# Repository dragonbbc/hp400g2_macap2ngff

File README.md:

# HP ProDesk 400 G2 Desktop Mini PC专用的94360CS2转接卡
将网卡接口往SSD移动了一点，完美避开电容

网卡的座子找了好久也没找到到哪里可以买到（有知道的兄弟烦请告知），现在是从别的转接卡上拆了一个装过去的
# 安装效果图

# 食用方法
直接下载gerber拿去JLC打板就好，板厚选0.8，不做沉金工艺的话5元包邮即可，土豪请随意。

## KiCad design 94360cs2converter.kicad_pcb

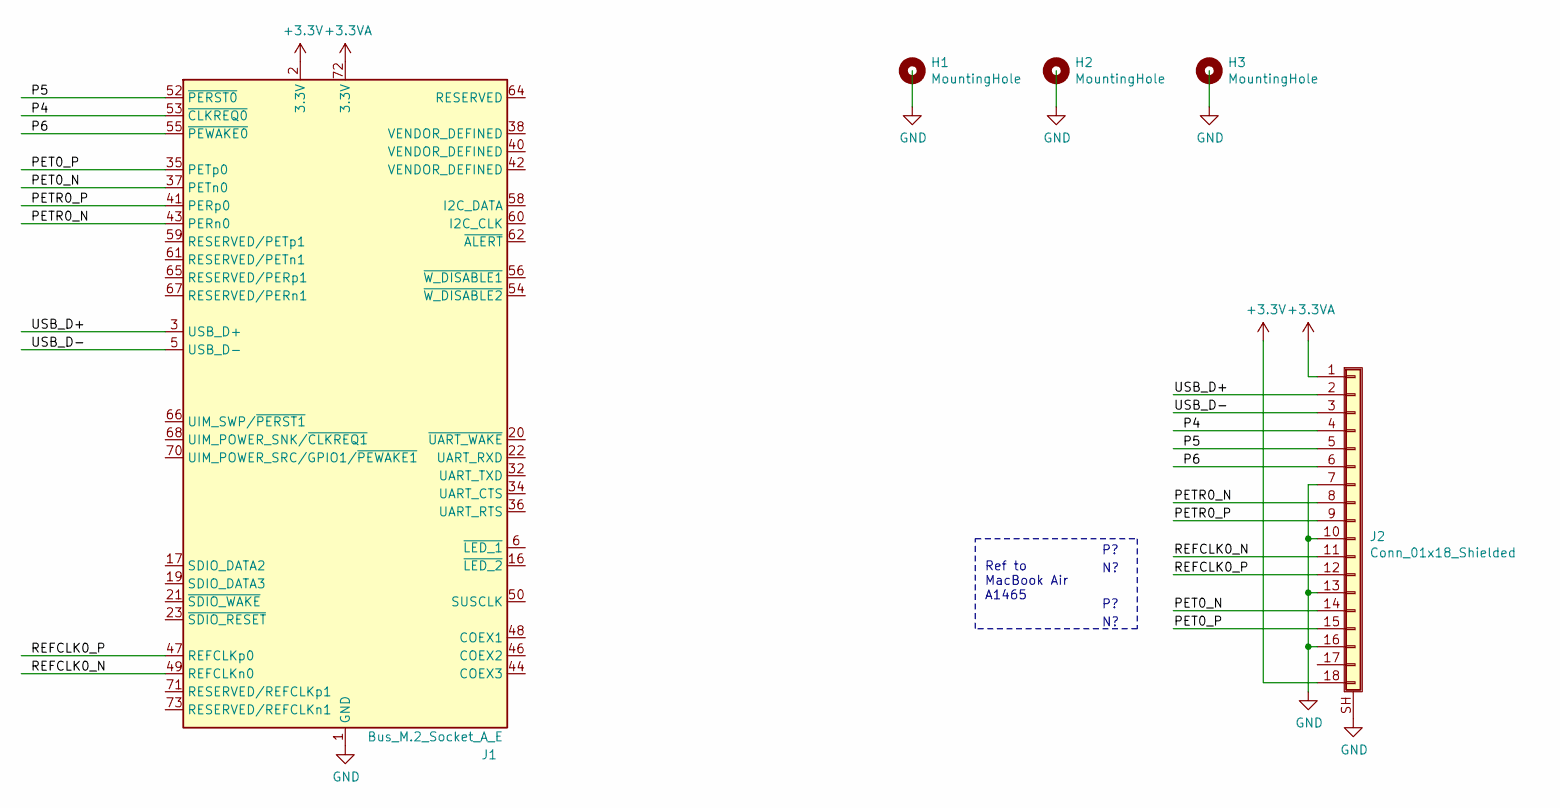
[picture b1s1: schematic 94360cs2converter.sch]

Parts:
H1: MountingHole; MountingHole_3mm_Pad_Via
H2, H3: MountingHole; MountingHole_3mm_Pad
J1: Bus_M.2_Socket_A_E; NGFF_A_E
J2: Conn_01x18_Shielded; MacWifiSocket

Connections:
+3.3VA: J1.72 (3.3V), J1.74 (3.3V), J2.1
+3V3: J1.2 (3.3V), J1.4 (3.3V), J2.18
/P4: J1.53 (~CLKREQ0), J2.4
/P5: J1.52 (~PERST0), J2.5
/P6: J1.55 (~PEWAKE0), J2.6
/PET0_N: J1.37 (PETn0), J2.14
/PET0_P: J1.35 (PETp0), J2.15
/PETR0_N: J1.43 (PERn0), J2.8
/PETR0_P: J1.41 (PERp0), J2.9
/REFCLK0_N: J1.49 (REFCLKn0), J2.11
/REFCLK0_P: J1.47 (REFCLKp0), J2.12
/USB_D+: J1.3 (USB_D+), J2.2
/USB_D-: J1.5 (USB_D-), J2.3
GND: H1.1, H2.1, H3.1, J1.1 (GND), J1.7 (GND), J1.18 (GND), J1.33 (GND), J1.39 (GND), J1.45 (GND), J1.51 (GND), J1.57 (GND), J1.63 (GND), J1.69 (GND), J1.75 (GND), J2.7, J2.10, J2.13, J2.16, J2.SH (Shield)

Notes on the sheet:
Ref to MacBook Air A1465

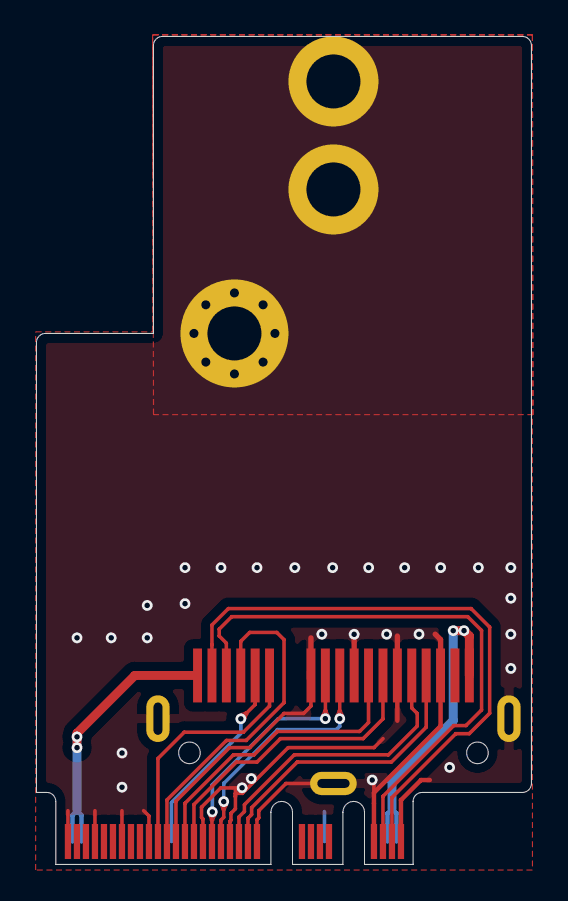
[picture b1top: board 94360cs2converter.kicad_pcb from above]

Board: 2 copper layers, 27.5 x 46.0 mm, 5 parts (0 on the bottom side), 14 nets.

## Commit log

2020-11-26 增加安装效果图
2020-11-26 更换效果图为小一点的照片
